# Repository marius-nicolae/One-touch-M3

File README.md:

# One-touch-M3
Arduino based One-touch module for Renault Megane III and compatible models.

For more info see the project's homepage https://create.arduino.cc/projecthub/Mne/one-touch-module-for-renault-megane-3-a89e3c?ref=user&ref_id=706679&offset=0 .

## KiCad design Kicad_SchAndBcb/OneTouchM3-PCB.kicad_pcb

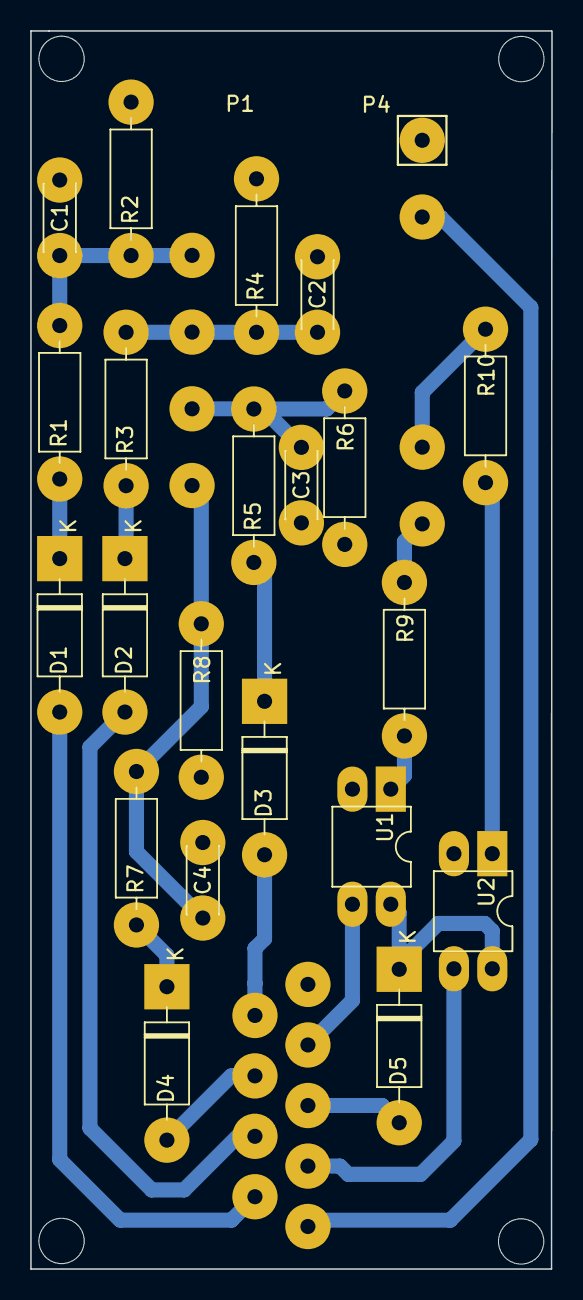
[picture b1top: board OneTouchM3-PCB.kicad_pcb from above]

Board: 2 copper layers, 34.5 x 82.0 mm, 24 parts (0 on the bottom side), 22 nets.

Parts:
C1, C2, C3, C4: 100n; C
D1, D2, D3, D4, D5: 1N4007; D
J3: Car connector; Car_connector
P1: Digital; P1_digital
P4: Analog; P4_analog
R1, R3, R5, R7: 100k; R
R2, R4, R6, R8: 47k; R
R9, R10: 220; R
U1, U2: EL817; Optocoupler

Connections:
/Common_BCM: D5.2, J3.3
/D2: C1.1, P1.5, R1.2, R2.1
/D4: C2.1, P1.7, R3.2, R4.1
/D6: C3.1, P1.9, R5.2, R6.1
/D8: C4.1, P1.11, R7.2, R8.1
/D10_(SS): P4.12, R9.1
/D12_MISO: P4.10, R10.1
/Left_BCM: J3.4, U2.3
/Left_blink: D4.2, J3.7
/Left_turn_sw: D2.2, J3.8
/Right_BCM: J3.2, U1.3
/Right_blink: D3.2, J3.6
/Right_turn_sw: D1.2, J3.9
GND: C1.2, C2.2, C3.2, C4.2, J3.1, P4.2, R2.2, R4.2, R6.2, R8.2, U1.2, U2.2
unnamed: D1.1, R1.1
unnamed: D2.1, R3.1
unnamed: D3.1, R5.1
unnamed: D4.1, R7.1
unnamed: D5.1, U1.4, U2.4
unnamed: R9.2, U1.1
unnamed: R10.2, U2.1
VCC: J3.5, P4.4

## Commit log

2019-08-19 Initial import
